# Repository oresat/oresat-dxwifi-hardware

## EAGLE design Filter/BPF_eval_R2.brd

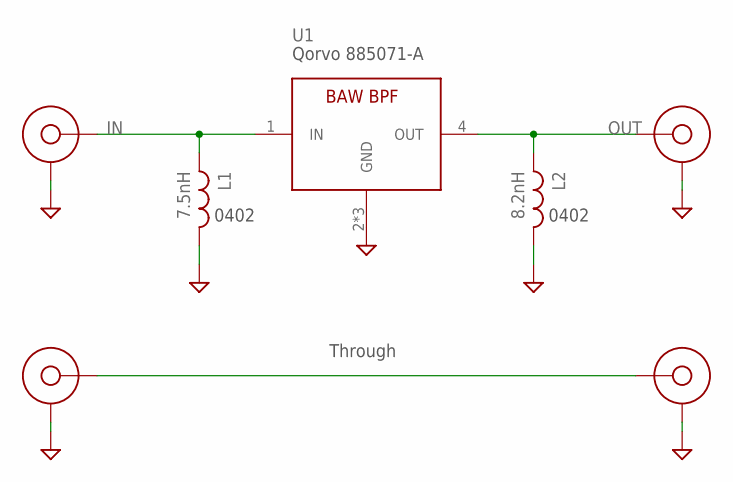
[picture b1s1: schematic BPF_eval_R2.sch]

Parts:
CF1, CF2, CF3, CF4: SMA-CINCH-END-FIRE; SMAJ716-ND
L1: 7.5nH; .0402-B-NOSILK
L2: 8.2nH; .0402-B-NOSILK
U1: 885071-A; FIL_B39162B9417K610

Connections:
GND: CF1.GND1 (GND), CF1.GND2 (GND), CF1.GND3 (GND), CF1.GND4 (GND), CF2.GND1 (GND), CF2.GND2 (GND), CF2.GND3 (GND), CF2.GND4 (GND), CF3.GND1 (GND), CF3.GND2 (GND), CF3.GND3 (GND), CF3.GND4 (GND), CF4.GND1 (GND), CF4.GND2 (GND), CF4.GND3 (GND), CF4.GND4 (GND), L1.2, L2.2, U1.2 (GND), U1.3 (GND), U1.5 (GND)
IN: CF1.P$3 (CENTERCONDUCTOR), L1.1, U1.1 (IN)
OUT: CF3.P$3 (CENTERCONDUCTOR), L2.1, U1.4 (OUT)
THROUGH: CF2.P$3 (CENTERCONDUCTOR), CF4.P$3 (CENTERCONDUCTOR)

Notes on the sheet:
0402
Qorvo 885071-A
Through

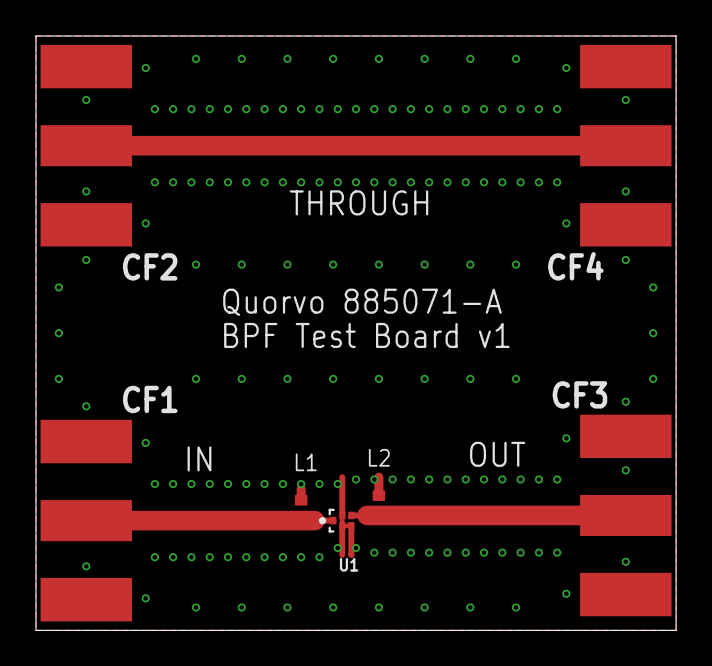
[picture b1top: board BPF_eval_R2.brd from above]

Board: 4 copper layers, 35.6 x 33.0 mm, 7 parts (0 on the bottom side), 4 nets.

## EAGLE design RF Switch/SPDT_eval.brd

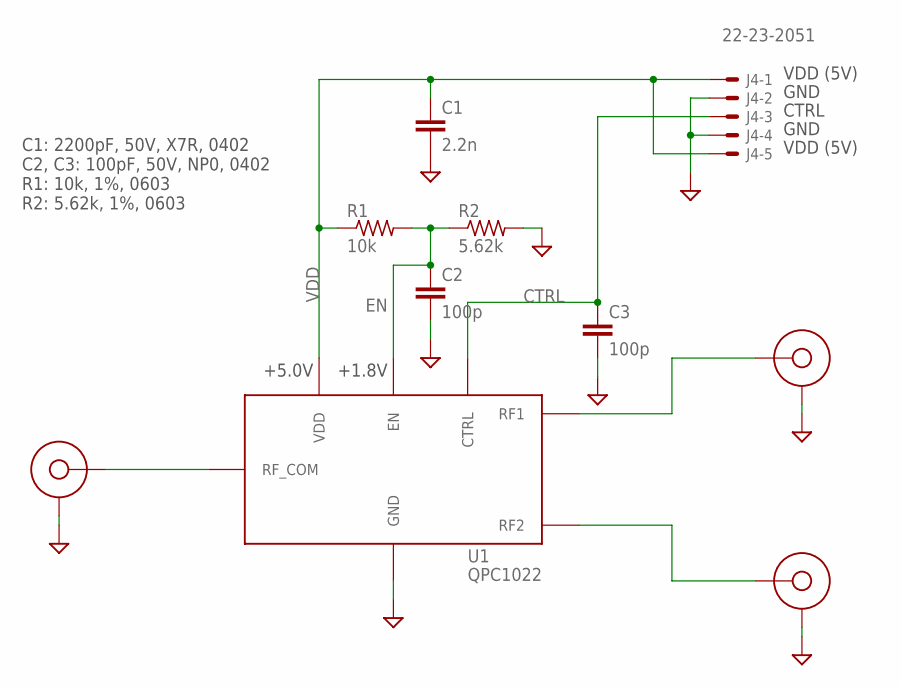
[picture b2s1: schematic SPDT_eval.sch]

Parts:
C1: 2.2n; .0402-B-NOSILK
C2, C3: 100p; .0402-B-NOSILK
CF1, CF2, CF3: SMA-CINCH-END-FIRE; SMAJ716-ND
J4: 22-23-2051
R1: 10k; .0603-B-NOSILK
R2: 5.62k; .0603-B-NOSILK
U1: QPC1022

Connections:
COM: CF1.P$3 (CENTERCONDUCTOR), U1.ANT (RF_COM)
CTRL: C3.1, J4.3, U1.CTRL
EN: C2.1, R1.2, R2.1, U1.EN
GND: C1.2, C2.2, C3.2, CF1.GND1 (GND), CF1.GND2 (GND), CF1.GND3 (GND), CF1.GND4 (GND), CF2.GND1 (GND), CF2.GND2 (GND), CF2.GND3 (GND), CF2.GND4 (GND), CF3.GND1 (GND), CF3.GND2 (GND), CF3.GND3 (GND), CF3.GND4 (GND), J4.2, J4.4, R2.2, U1.GND@1 (GND), U1.GND@2 (GND), U1.GND@3 (GND)
RF1: CF2.P$3 (CENTERCONDUCTOR), U1.RF1
RF2: CF3.P$3 (CENTERCONDUCTOR), U1.RF2
VDD: C1.1, J4.1, J4.5, R1.1, U1.VDD

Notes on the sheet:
C1: 2200pF, 50V, X7R, 0402 C2, C3: 100pF, 50V, NP0, 0402 R1: 10k, 1%, 0603 R2: 5.62k, 1%, 0603
+5.0V
+1.8V
VDD (5V)
GND
CTRL

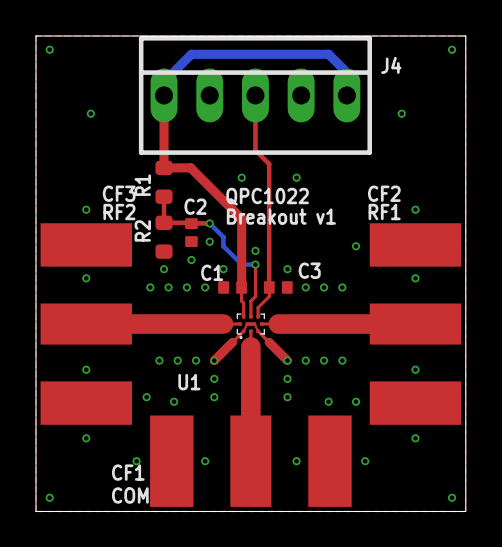
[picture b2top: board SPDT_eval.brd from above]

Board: 4 copper layers, 23.9 x 26.4 mm, 10 parts (0 on the bottom side), 7 nets.
